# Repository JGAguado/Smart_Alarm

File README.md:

[![Documentation Status][documentation-shield]][documentation]
[![GitHub Release][releases-shield]][releases]
[![License][license-shield]](LICENSE)

[![Project Maintenance][maintenance-shield]][maintenance]
[![BuyMeCoffee][buymecoffee-shield]][buymecoffee]

# Smart Alarm
The Smart Alarm is an ESP32-CAM compatible board that integrates a PIR sensor and direct connection with a R503 fingerprint reader device.

## Project tree
---
<li><a href="./Design/">Design</a></li>
<li><a href="./Documentation/">Documentation</a></li>

<li><a href="./README.md">README.md</a></li>

[documentation-shield]: https://readthedocs.org/projects/smart-alarm/badge/?version=latest&style=for-the-badge
[documentation]: https://smart-alarm.readthedocs.io/en/latest/

[releases-shield]: https://img.shields.io/github/release/JGAguado/Smart_Alarm.svg?style=for-the-badge
[releases]: https://github.com/JGAguado/Smart_Alarm/releases

[license-shield]: https://img.shields.io/badge/License-CC%20BY--NC--SA%204.0-lightgrey.svg?style=for-the-badge

[maintenance-shield]: https://img.shields.io/badge/maintainer-J.%20G.%20Aguado-blue.svg?style=for-the-badge
[maintenance]: https://github.com/JGAguado

[buymecoffee-shield]: https://img.shields.io/badge/buy%20me%20a%20coffee-support-yellow.svg?style=for-the-badge
[buymecoffee]: https://www.buymeacoffee.com/J.G.Aguado

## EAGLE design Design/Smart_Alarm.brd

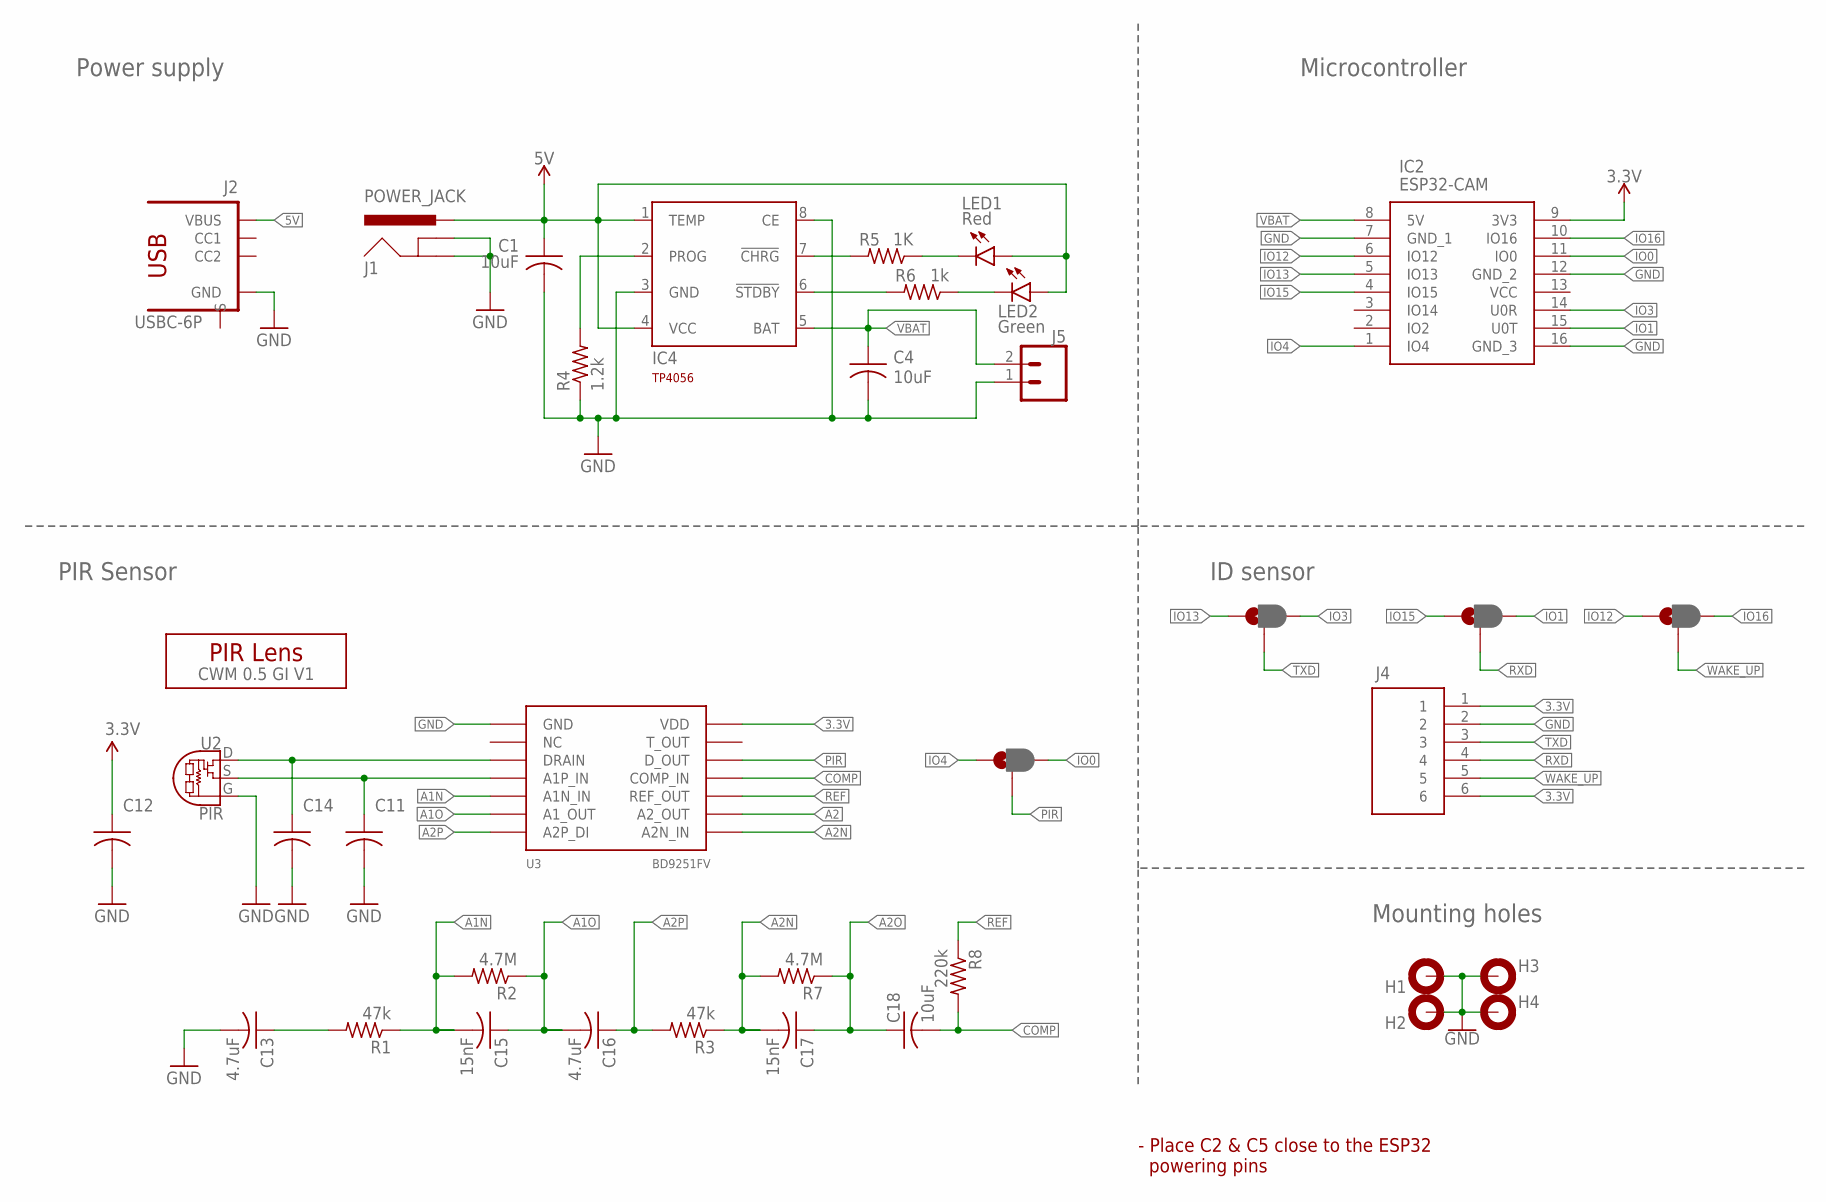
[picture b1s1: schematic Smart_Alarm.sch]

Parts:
C1, C4, C18: 10uF; C0603
C11, C12, C14: 1.0uF; C0603
C13, C16: 4.7uF; C0603
C15, C17: 15nF; C0603
H1, H2, H3, H4: MOUNT-PAD-ROUND; 3,0-PAD
IC2: ESP32-CAM; ESP32CAM
IC4: TP4056; SOT23-8
J1: POWER_JACK; POWER_JACK_PTH
J2: USBC-6P; USCX-06FX-XXMX-01
J4: JST_6_PIN_VERTICAL; JST-6-SMD-VERT-1.0MM
J5: CONN_02-JST-2-PTH-NO_SILK; JST-2-PTH-NS
JP1, JP2, JP3, JP4: JUMPER-SMT_3_1-NC_PASTE_NO-SILK; SMT-JUMPER_3_1-NC_PASTE_NO-SILK
LED1: Red; LED_0603
LED2: Green; LED_0603
R1, R3: 47k; R0603
R2, R7: 4.7M; R0603
R4: 1.2k; R0603
R5: 1K; R0603
R6: 1k; R0603
R8: 220k; R0603
U2: PIR
U3: BD9251FV; TSSOP-14
U$2: CWM 0.5 GI V1; LENS-CWM-0.5-GI-V1

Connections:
3.3V: C12.1, IC2.9 (3V3), J4.1, J4.6, U3.14 (VDD)
5V: C1.1, IC4.1 (TEMP), IC4.4 (VCC), J1.PWR, J2.VBUS1 (VBUS), J2.VBUS2 (VBUS), LED1.A, LED2.A
A1N: C15.2, R1.1, R2.2, U3.5 (A1N_IN)
A1O: C15.1, C16.2, R2.1, U3.6 (A1_OUT)
A2: U3.9 (A2_OUT)
A2N: C17.2, R3.1, R7.2, U3.8 (A2N_IN)
A2O: C17.1, C18.1, R7.1
A2P: C16.1, R3.2, U3.7 (A2P_DI)
COMP: C18.2, R8.2, U3.11 (COMP_IN)
GND: C1.2, C4.2, C11.2, C12.2, C13.2, C14.2, H1.B3,0, H1.P$2, H1.P$3, H1.P$4, H1.P$5, H1.P$6, H1.P$7, H1.P$8, H1.P$9, H2.B3,0, H2.P$2, H2.P$3, H2.P$4, H2.P$5, H2.P$6, H2.P$7, H2.P$8, H2.P$9, H3.B3,0, H3.P$2, H3.P$3, H3.P$4, H3.P$5, H3.P$6, H3.P$7, H3.P$8, H3.P$9, H4.B3,0, H4.P$2, H4.P$3, H4.P$4, H4.P$5, H4.P$6, H4.P$7, H4.P$8, H4.P$9, IC2.7 (GND_1), IC2.12 (GND_2), IC2.16 (GND_3), IC4.3 (GND), IC4.8 (CE), J1.GND, J1.GNDBREAK, J2.GND1 (GND), J2.GND2 (GND), J4.2, J5.1, R4.1, U2.G, U3.1 (GND)
IO0: IC2.11 (IO0), JP4.3
IO1: IC2.15 (U0T), JP2.3
IO3: IC2.14 (U0R), JP1.3
IO4: IC2.1 (IO4), JP4.1
IO12: IC2.6 (IO12), JP3.1
IO13: IC2.5 (IO13), JP1.1
IO15: IC2.4 (IO15), JP2.1
IO16: IC2.10 (IO16), JP3.3
unnamed: LED1.C, R5.1
unnamed: IC4.6 (!STDBY), R6.2
unnamed: LED2.C, R6.1
unnamed: IC4.2 (PROG), R4.2
unnamed: IC4.7 (!CHRG), R5.2
unnamed: C11.1, U2.S, U3.4 (A1P_IN)
unnamed: C14.1, U2.D, U3.3 (DRAIN)
unnamed: C13.1, R1.2
PIR: JP4.2, U3.12 (D_OUT)
REF: R8.1, U3.10 (REF_OUT)
RXD: J4.4, JP2.2
TXD: J4.3, JP1.2
VBAT: C4.1, IC2.8 (5V), IC4.5 (BAT), J5.2
WAKE_UP: J4.5, JP3.2

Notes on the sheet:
- Place C2 & C5 close to the ESP32 powering pins
PIR Sensor
Mounting holes
Microcontroller
Power supply
ID sensor

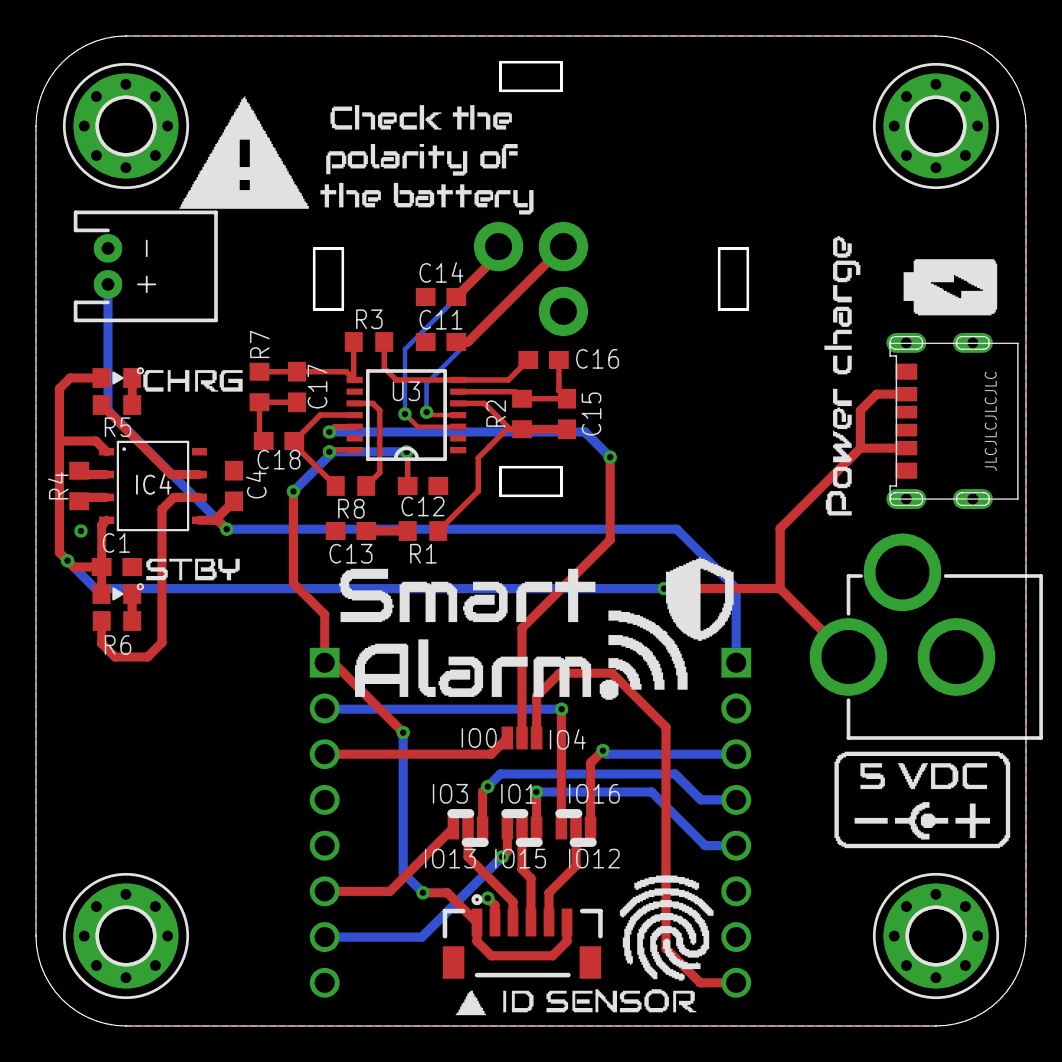
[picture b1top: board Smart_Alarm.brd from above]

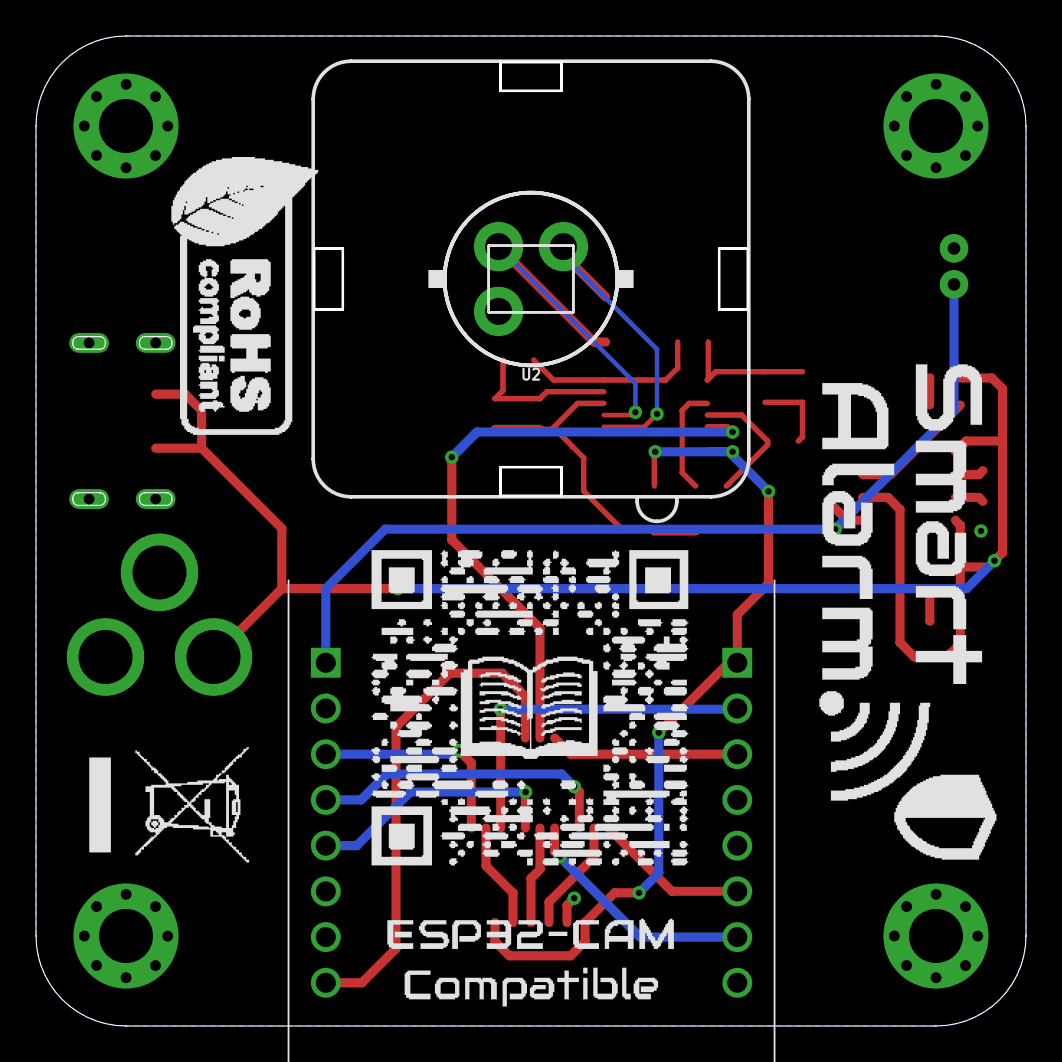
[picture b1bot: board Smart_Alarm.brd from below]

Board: 2 copper layers, 54.9 x 54.9 mm, 37 parts (3 on the bottom side), 31 nets.

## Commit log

2022-11-01 docs

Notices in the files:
parts and their libraries:
SparkFun-Connectors: Licensing: Creative Commons ShareAlike 4.0 International - https://creativecommons.org/licenses/by-sa/4.0
